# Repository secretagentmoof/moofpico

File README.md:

moofpico, a clone of a2pico 2.x (aka A2retronet RP2040)

This is a mostly-clone of the 2.4 through-hole [a2pico pcb board](https://github.com/rallepalaveev/a2pico), mostly for use as an Apple II <-> SD card interface, with a few minor tweaks. Why use this instead of one of the other boards out there? Mostly: no (E(E))PROMs, no PALs, nothing that needs to be programmed outside of using the Pico's USB connection - and designed so that almost all of the parts can be pretty easily hand-soldered.

The [RPi Pico datasheet](https://datasheets.raspberrypi.com/pico/pico-datasheet.pdf) explains some aspects that aren't made clear in either the schematic or its board symbol:
- the `3V3` pin is 3.3V in *and* out from the Pi unit; it's used to power both the RPi itself and can supply 300mA to other circuitry. Normally it's generated internally from...
- the `VSYS` pin is the main system input voltage (accepts 1.8V-5.5V); in our case, we can power it either from the apple II +5V slot, or from...
- the `VBUS` pin is connected to the uUSB pin1 connector; it can thus be used to power the unit when the Apple II itself is off, and...
- in section 4.5 they explicitly note how you should combine multiple power sources (VSYS + Schottky). TBH, I'm not sure why the DIP switch is needed.
- You can reset the RPi by pulling `RUN` low, or power the unit down entirely by pulling `3V3_EN` low.

While I don't think I'm allowed to redistribute the MEM2061 uSD socket footprint/3D model, you can grab it from DigiKey's model page: https://www.digikey.com/en/models/9859612 (the SnapMagic one). I've used the KiCad schematic symbol, even though it only has 11 pins and not 12 (extra is just shield ground).

The dimensions for apple2 peripheral cards is defined in IIgs tech note #28, https://mirrors.apple2.org.za/ftp.gno.org/doc/apple/technotes/iigs/tn.iigs.028

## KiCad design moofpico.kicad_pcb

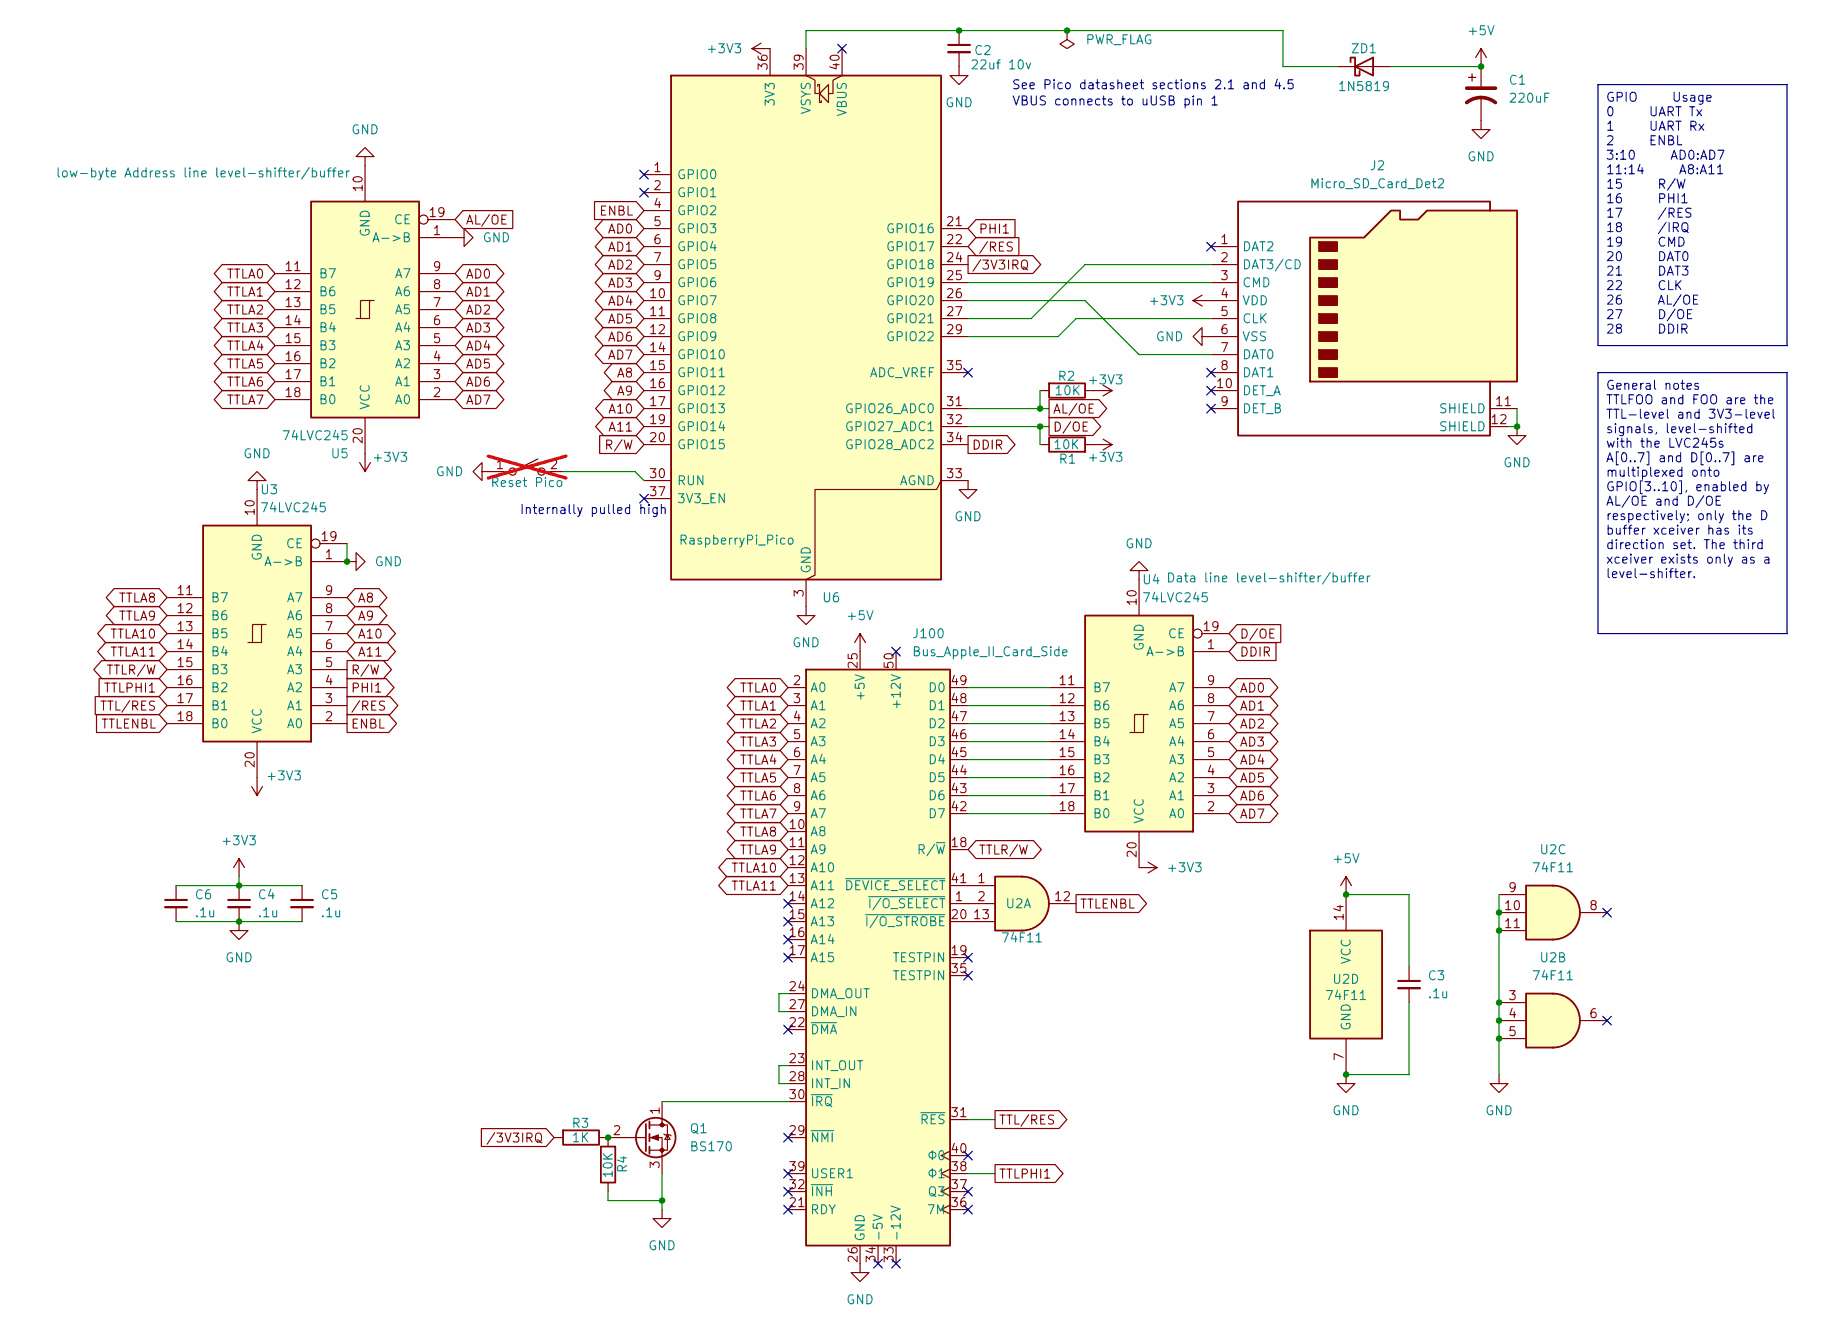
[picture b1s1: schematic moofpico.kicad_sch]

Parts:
C1: 220uF; CP_Radial_D6.3mm_P2.50mm
C2: 22uf 10v; C_Disc_D5.0mm_W2.5mm_P2.50mm
C3, C4, C5, C6: .1u; C_Disc_D3.8mm_W2.6mm_P2.50mm
J2: Micro_SD_Card_Det2; GCT_MEM2061-01-188-00-A_REVA
J100: Bus_Apple_II_Card_Side; Peripheral_Bus_Edge
Q1: BS170; TO-92_Inline
R1, R2, R4: 10K; R_Axial_DIN0207_L6.3mm_D2.5mm_P7.62mm_Horizontal
R3: 1K; R_Axial_DIN0207_L6.3mm_D2.5mm_P7.62mm_Horizontal
SW1: SW_SPST; PinSocket_1x02_P1.27mm_Vertical; not fitted
U2: 74F11; DIP-14_W7.62mm_Socket
U3, U4, U5: 74LVC245; DIP-20_W7.62mm_Socket
U6: RaspberryPi_Pico; RaspberryPi_Pico_Common
ZD1: 1N5819; D_DO-41_SOD81_P7.62mm_Horizontal

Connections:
+3V3: C4.1, C5.1, C6.1, J2.4 (VDD), R1.2, R2.1, U3.20 (VCC), U4.20 (VCC), U5.20 (VCC), U6.36 (3V3)
+5V: C1.1, C3.1, J100.25 (+5V), U2.14 (VCC), ZD1.2 (A)
A8: U3.9 (A7), U6.15 (GPIO11)
A9: U3.8 (A6), U6.16 (GPIO12)
A10: U3.7 (A5), U6.17 (GPIO13)
A11: U3.6 (A4), U6.19 (GPIO14)
AD0: U4.9 (A7), U5.9 (A7), U6.5 (GPIO3)
AD1: U4.8 (A6), U5.8 (A6), U6.6 (GPIO4)
AD2: U4.7 (A5), U5.7 (A5), U6.7 (GPIO5)
AD3: U4.6 (A4), U5.6 (A4), U6.9 (GPIO6)
AD4: U4.5 (A3), U5.5 (A3), U6.10 (GPIO7)
AD5: U4.4 (A2), U5.4 (A2), U6.11 (GPIO8)
AD6: U4.3 (A1), U5.3 (A1), U6.12 (GPIO9)
AD7: U4.2 (A0), U5.2 (A0), U6.14 (GPIO10)
AL/OE: R2.2, U5.19 (CE), U6.31 (GPIO26_ADC0)
DDIR: U4.1 (A->B), U6.34 (GPIO28_ADC2)
D/OE: R1.1, U4.19 (CE), U6.32 (GPIO27_ADC1)
ENBL: U3.2 (A0), U6.4 (GPIO2)
GND: C1.2, C2.2, C3.2, C4.2, C5.2, C6.2, J2.6 (VSS), J2.11 (SHIELD), J2.12 (SHIELD), J100.26 (GND), Q1.3 (S), R4.1, SW1.1 (A), U2.3, U2.4, U2.5, U2.7 (GND), U2.9, U2.10, U2.11, U3.1 (A->B), U3.10 (GND), U3.19 (CE), U4.10 (GND), U5.1 (A->B), U5.10 (GND), U6.3 (GND), U6.8 (GND), U6.13 (GND), U6.18 (GND), U6.23 (GND), U6.28 (GND), U6.33 (AGND), U6.38 (GND)
unnamed: J2.5 (CLK), U6.29 (GPIO22)
unnamed: J2.3 (CMD), U6.25 (GPIO19)
unnamed: J2.7 (DAT0), U6.26 (GPIO20)
unnamed: J2.2 (DAT3/CD), U6.27 (GPIO21)
unnamed: J100.49 (D0), U4.11 (B7)
unnamed: J100.48 (D1), U4.12 (B6)
unnamed: J100.47 (D2), U4.13 (B5)
unnamed: J100.46 (D3), U4.14 (B4)
unnamed: J100.45 (D4), U4.15 (B3)
unnamed: J100.44 (D5), U4.16 (B2)
unnamed: J100.43 (D6), U4.17 (B1)
unnamed: J100.42 (D7), U4.18 (B0)
unnamed: J100.24 (DMA_OUT), J100.27 (DMA_IN)
unnamed: J100.23 (INT_OUT), J100.28 (INT_IN)
unnamed: J100.41 (~DEVICE_SELECT), U2.1
unnamed: J100.30 (~IRQ), Q1.1 (D)
unnamed: J100.1 (~I/O_SELECT), U2.2
unnamed: J100.20 (~I/O_STROBE), U2.13
unnamed: Q1.2 (G), R3.1, R4.2
unnamed: SW1.2 (B), U6.30 (RUN)
unnamed: C2.1, U6.39 (VSYS), ZD1.1 (K)
PHI1: U3.4 (A2), U6.21 (GPIO16)
R/W: U3.5 (A3), U6.20 (GPIO15)
TTLA0: J100.2 (A0), U5.11 (B7)
TTLA1: J100.3 (A1), U5.12 (B6)
TTLA2: J100.4 (A2), U5.13 (B5)
TTLA3: J100.5 (A3), U5.14 (B4)
TTLA4: J100.6 (A4), U5.15 (B3)
TTLA5: J100.7 (A5), U5.16 (B2)
TTLA6: J100.8 (A6), U5.17 (B1)
TTLA7: J100.9 (A7), U5.18 (B0)
TTLA8: J100.10 (A8), U3.11 (B7)
TTLA9: J100.11 (A9), U3.12 (B6)
TTLA10: J100.12 (A10), U3.13 (B5)
TTLA11: J100.13 (A11), U3.14 (B4)
TTLENBL: U2.12, U3.18 (B0)
TTLPHI1: J100.38 (Φ1), U3.16 (B2)
TTLR/W: J100.18 (R/~W), U3.15 (B3)
TTL/RES: J100.31 (~RES), U3.17 (B1)
/3V3‏IRQ: R3.2, U6.24 (GPIO18)
/RES: U3.3 (A1), U6.22 (GPIO17)

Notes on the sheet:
General notes TTLFOO and FOO are the TTL-level and 3V3-level signals, level-shifted with the LVC245s A[0..7] and D[0..7] are multiplexed onto GPIO[3..10], enabled by AL/OE and D/OE respectively; only the D buffer xceiver has its direction set. The third xceiver exists only as a level-shifter.
GPIO Usage 0 UART Tx 1 UART Rx 2 ENBL 3:10 AD0:AD7 11:14 A8:A11 15 R/W 16 PHI1 17 /RES 18 /IRQ 19 CMD 20 DAT0 21 DAT3 22 CLK 26 AL/OE 27 D/OE 28 DDIR
See Pico datasheet sections 2.1 and 4.5
VBUS connects to uUSB pin 1
Internally pulled high

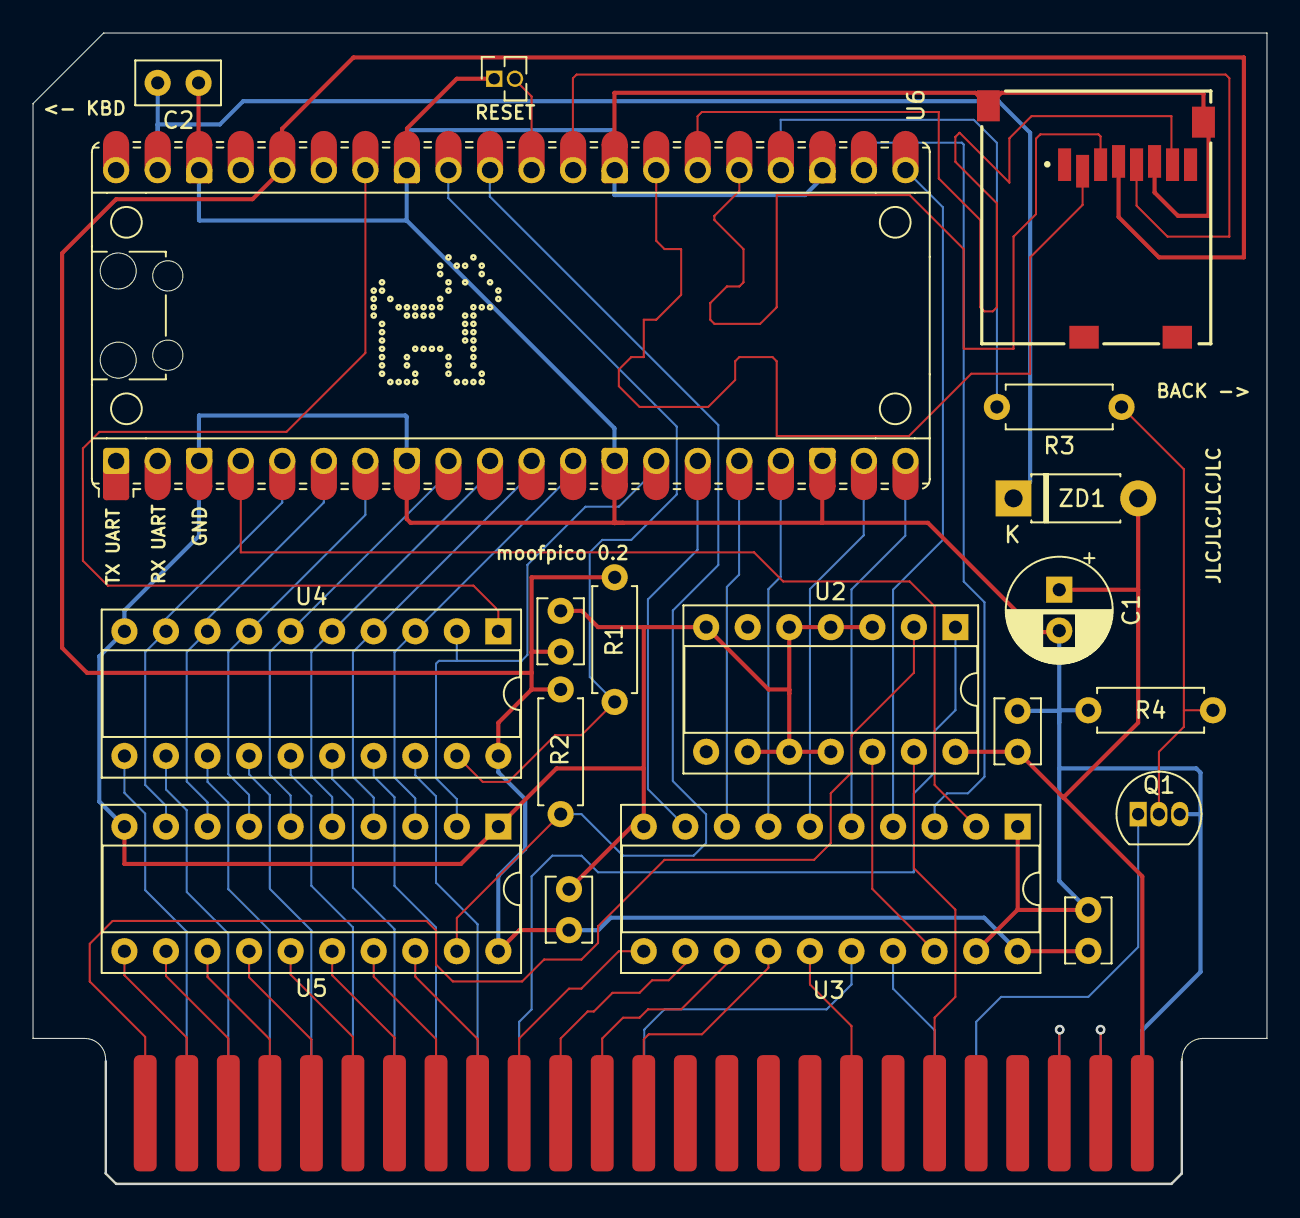
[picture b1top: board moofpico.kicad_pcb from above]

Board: 2 copper layers, 75.3 x 70.3 mm, 20 parts (0 on the bottom side), 60 nets.

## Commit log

2024-03-08 moofpico, a clone of the 2.x through-hole a2pico
2024-03-14 fix submodules
    track libraries/footprints
    track libraries/footprints
2024-03-14 resync w/ libraries
    add fp/sym for MEM2061
    pretty sure I can't redistribute the MEM2061 footprints, alas
2024-03-14 make +3V3 and GND a little thicker; move +3V3 trace out from between some other RPi traces and onto its own test point/header pin/quasi-via
    faffing about with power and ground
    but *why*?
2024-03-14 use MEM2061 instead of "generic" SD
2024-03-14 update datasheet URLs; add extra shield pin to uSD
    more accurately specify capacitor size
    nudged rpi over so that it sat on the mill grid
    more footprint futzing
    move to 5 pin serial/power connector
2024-03-14 remove the interior two layers; should have never been there to begin with
    notey notey note
2024-03-14 got rid of the vias
    don't sneak by that stupid square pin
2024-03-14 checkpoint: moved the SD card around
2024-03-14 more minor trace tweaking
2024-03-14 use ki-lime-pi-pico footprint, since it has a bunch of extra stuff (keepouts and holes) - which required rerouting a whole bunch of stuff
    labels, whee
2024-03-14 fix paths for 3d model
2024-03-14 I do love how resynchronizing with the schematic changes all the UUIDs
2024-03-15 this side towards enemy
2024-03-17 more faffing about with moving components
2024-03-25 checkpoint: kicad 8.0.1, move components around
2024-03-26 move footprint so that the card edges are aligned with the (mil) grid
2024-03-26 probably voodoo at this point, but: add another decoupling cap (although I seriously doubt it's needed at this point) provide enough space on the board so q1, c1, and f1 can all be bent flat
2024-03-26 more movin'
2024-03-28 swap nand pin assignments around
2024-03-28 more probably needless shuffling around of components
2024-03-29 ground unused NAND inputs
2024-03-30 silkscreening
2024-03-30 muck about with silkscreen; deem version 0.1
2024-04-10 fodder for search engines
2024-04-10 move to 1x dip (even though it's more expensive than 2x?); swap enbl and phi1 to make the pcb layout ever so slightly nicer
2024-04-21 minor fiddling, NFCI
2024-04-24 more gratuitous track fiddling
2024-04-27 major design change: get rid of the uart headers and usb power dip switch I'm not convinced they're actually needed, and the stuff around the USB power in the pico manual makes me think it's superflu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
2024-05-01 add (unpopulated) reset button for pico; fix direction of IRQ (NFCI)
2024-05-24 equalize SD track lengths
2024-05-25 silly colinear tracks messed up the total length calculation, sigh
2024-06-18 honestly, don't remember - and kicad changes stuff arbitrarily anyway
2024-07-29 updated pi and apple II slots; NFCI
2024-07-29 stupid line endings
